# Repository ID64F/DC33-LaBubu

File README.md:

# DC33-LaBubu

## JLCPCB PCB Colors & Components
- ENIG Copper
- White Silk
- Mask
    * Red
    * Blue
    * Purple
    * Green 
    * Yellow
    * White
    * Black
- Components
    * 1206 SMD LEDs HandSoldering
    * 1206 SMD Resistors HandSoldering
    * 1206 SMD Capacitor HandSoldering
    * Attiny85
    * MCP23017
    * CR2032 Battery Holder
    * Switch
    * SAO Connector
<div align="center">

</div>
<div align="center">
 
</div>

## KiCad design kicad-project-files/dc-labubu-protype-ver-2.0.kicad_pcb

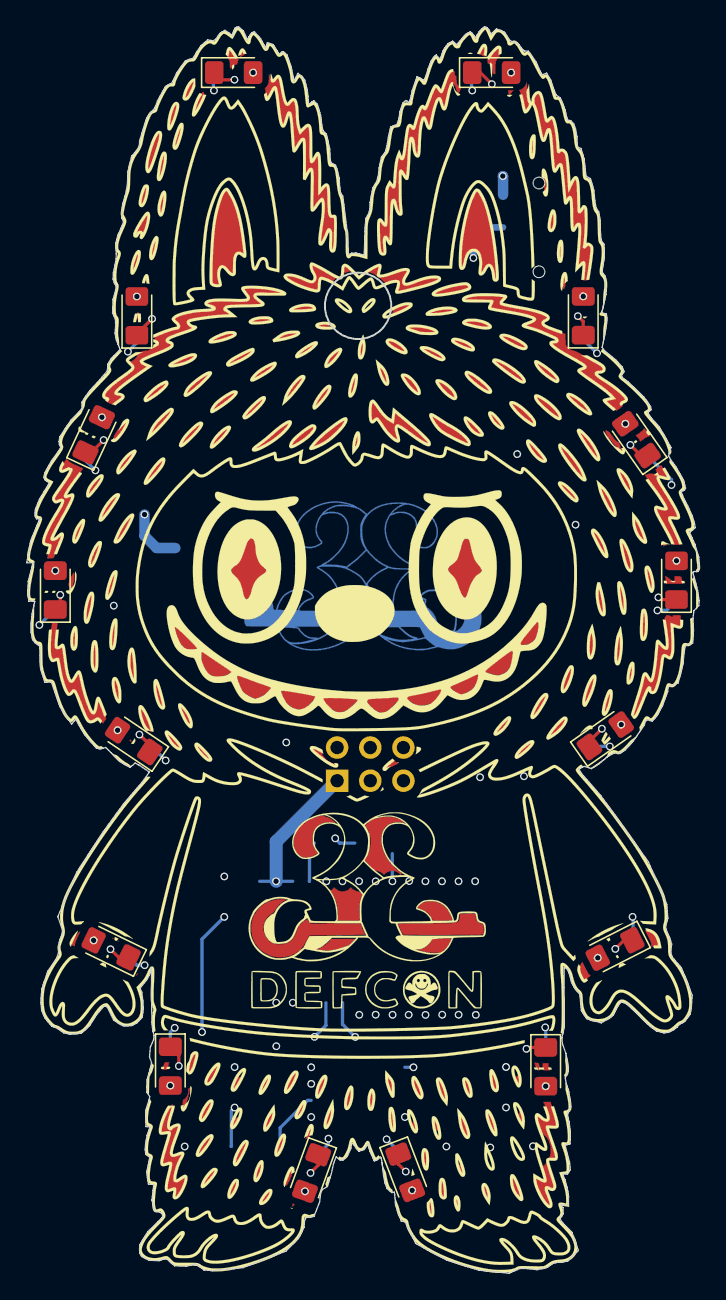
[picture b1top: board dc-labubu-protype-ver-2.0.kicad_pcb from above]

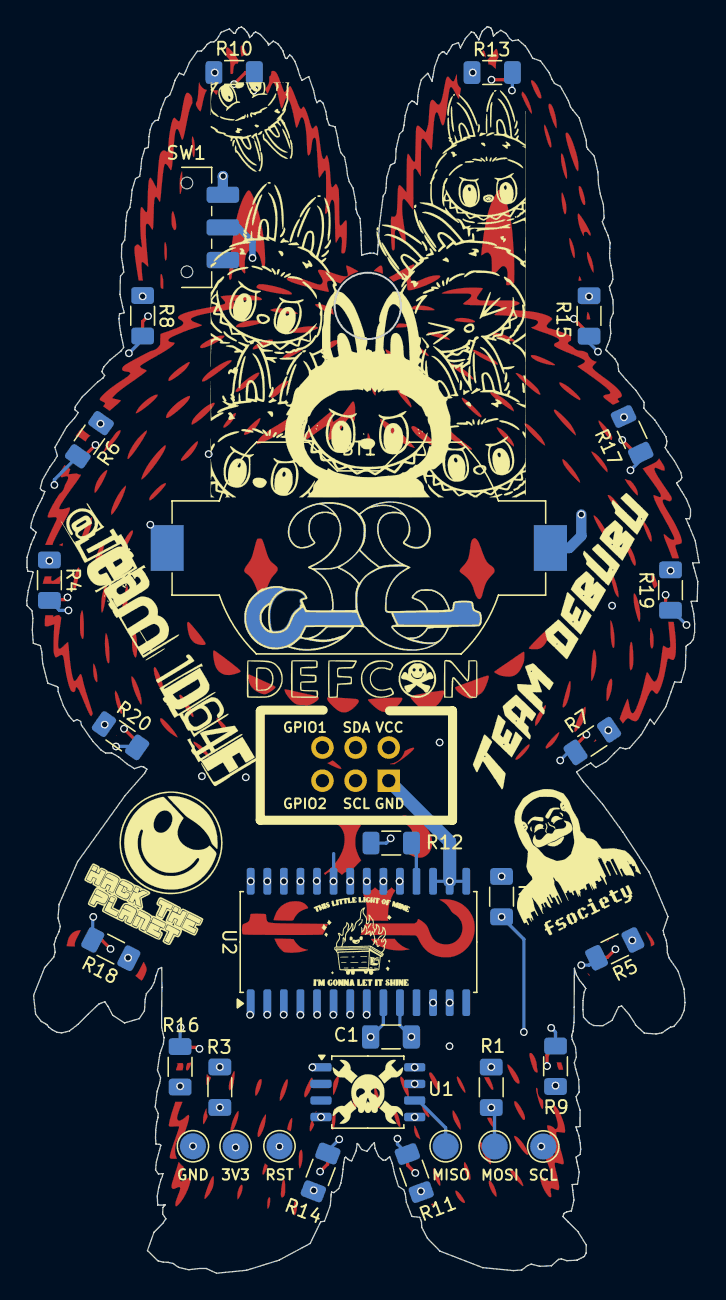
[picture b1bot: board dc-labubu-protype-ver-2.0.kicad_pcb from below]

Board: 4 copper layers, 51.5 x 95.4 mm, 49 parts (31 on the bottom side), 42 nets.

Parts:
3V3: +3V3; TestPoint_Pad_D2.0mm
BT1: Battery_Cell; BatteryHolder_Keystone_1058_1x2032
C1: 0.1µF; C_1206_3216Metric_Pad1.33x1.80mm_HandSolder
D1, D2, D3, D4, D5, D6, D7, D8, D9, D10, D11, D12, D13, D14, D15, D16: LED; LED_1206_3216Metric_Pad1.42x1.75mm_HandSolder
GND: GND; TestPoint_Pad_D2.0mm
MISO: MISO; TestPoint_Pad_D2.0mm
MOSI: MOSI (SDA); TestPoint_Pad_D2.0mm
R1, R2: 4.7k; R_1206_3216Metric_Pad1.30x1.75mm_HandSolder
R3, R12: 10kΩ; R_1206_3216Metric_Pad1.30x1.75mm_HandSolder
R4, R5, R6, R7, R8, R9, R10, R11, R13, R14, R15, R16, R17, R18, R19, R20: 220Ω; R_1206_3216Metric_Pad1.30x1.75mm_HandSolder
RST: RESET; TestPoint_Pad_D2.0mm
Ref**: Val**; dc-labubu-protype-ver-2.0
SCL: SCK (SCL); TestPoint_Pad_D2.0mm
SW1: SW_SPST; SW_SPDT_CK_JS102011SAQN
U1: ATtiny85-20S; SOIC-8_5.3x5.3mm_P1.27mm
U2: MCP23017_SO; SOIC-28W_7.5x17.9mm_P1.27mm
X1: Badgelife_sao_connector_v169bis; Badgelife-SAOv169-SAO-2x3

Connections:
+3V3: 3V3.1, C1.2, R1.1, R2.1, R3.1, R12.2, SW1.2 (B), U1.8 (VCC), U2.9 (VDD), X1.1 (VCC)
/BAT+: BT1.1 (+), SW1.1 (A)
/GPA0: R19.2, U2.21 (GPA0)
/GPA1: R17.2, U2.22 (GPA1)
/GPA2: R15.2, U2.23 (GPA2)
/GPA3: R13.2, U2.24 (GPA3)
/GPA4: R10.2, U2.25 (GPA4)
/GPA5: R8.2, U2.26 (GPA5)
/GPA6: R6.2, U2.27 (GPA6)
/GPA7: R4.2, U2.28 (GPA7)
/GPB0: R20.2, U2.1 (GPB0)
/GPB1: R18.2, U2.2 (GPB1)
/GPB2: R16.2, U2.3 (GPB2)
/GPB3: R14.2, U2.4 (GPB3)
/GPB4: R11.2, U2.5 (GPB4)
/GPB5: R9.2, U2.6 (GPB5)
/GPB6: R7.2, U2.7 (GPB6)
/GPB7: R5.2, U2.8 (GPB7)
/GPIO1: U2.20 (INTA), X1.5 (GPIO1)
/GPIO2: U2.19 (INTB), X1.6 (GPIO2)
GND: BT1.2 (-), C1.1, D1.1 (K), D2.1 (K), D3.1 (K), D4.1 (K), D5.1 (K), D6.1 (K), D7.1 (K), D8.1 (K), D9.1 (K), D10.1 (K), D11.1 (K), D12.1 (K), D13.1 (K), D14.1 (K), D15.1 (K), D16.1 (K), GND.1, U1.4 (GND), U2.10 (VSS), U2.15 (A0), U2.16 (A1), U2.17 (A2), X1.2 (GND)
MISO: MISO.1, U1.6 (PB1)
MOSI: MOSI.1, R1.2, U1.5 (AREF/PB0), U2.13 (SDA), X1.3 (SDA)
unnamed: D1.2 (A), R4.1
unnamed: D2.2 (A), R5.1
unnamed: D3.2 (A), R6.1
unnamed: D4.2 (A), R7.1
unnamed: D5.2 (A), R8.1
unnamed: D6.2 (A), R9.1
unnamed: D7.2 (A), R10.1
unnamed: D8.2 (A), R11.1
unnamed: D9.2 (A), R13.1
unnamed: D10.2 (A), R14.1
unnamed: D11.2 (A), R15.1
unnamed: D12.2 (A), R16.1
unnamed: D13.2 (A), R17.1
unnamed: D14.2 (A), R18.1
unnamed: D15.2 (A), R19.1
unnamed: D16.2 (A), R20.1
unnamed: R12.1, U2.18 (~RESET)
RESET: R3.2, RST.1, U1.1 (~RESET/PB5)
SCL: R2.2, SCL.1, U1.7 (PB2), U2.12 (SCK), X1.4 (SCL)

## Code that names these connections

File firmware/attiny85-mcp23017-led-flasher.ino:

#include <Wire.h>
#include <avr/sleep.h>
#include <avr/power.h>
#include <avr/wdt.h>

// MCP23017 I2C address (A0, A1, A2 = LOW)
#define MCP23017_ADDR 0x20

// MCP23017 Register addresses
#define MCP23017_IODIRA   0x00  // I/O Direction Register A
#define MCP23017_IODIRB   0x01  // I/O Direction Register B
#define MCP23017_GPIOA    0x12  // General Purpose I/O Port Register A
#define MCP23017_GPIOB    0x13  // General Purpose I/O Port Register B

// ATtiny85 pins for I2C (using TinyWireM library pins)
// SDA = Pin 0 (PB0)
// SCL = Pin 2 (PB2)

volatile bool wakeUp = false;

void setup() {
  // Disable unused peripherals to save power
  power_adc_disable();
  power_timer1_disable();
  
  // Initialize I2C
  Wire.begin();
  Wire.setClock(100000); // 100kHz for lower power consumption
  
  // Initialize MCP23017
  initMCP23017();
  
  // Setup watchdog timer for 1 second intervals
  setupWatchdog();
  
  // Set sleep mode
  set_sleep_mode(SLEEP_MODE_PWR_DOWN);
}

void loop() {
  // Flash each LED for 500ms
  for (uint8_t port = 0; port < 2; port++) {
    for (uint8_t pin = 0; pin < 8; pin++) {
      // Turn on current LED
      setLED(port, pin, true);
      
      // Wait 500ms using watchdog timer (sleep)
      sleepFor500ms();
      
      // Turn off current LED
      setLED(port, pin, false);
    }
  }
  
  // After cycling through all LEDs, sleep for longer period
  // to conserve battery (optional - remove if continuous cycling desired)
  for (uint8_t i = 0; i < 10; i++) { // Sleep for ~10 seconds
    sleepFor1Second();
  }
}

void initMCP23017() {
  // Set all pins as outputs (0 = output, 1 = input)
  writeRegister(MCP23017_IODIRA, 0x00); // Port A all outputs
  writeRegister(MCP23017_IODIRB, 0x00); // Port B all outputs
  
  // Turn off all LEDs initially
  writeRegister(MCP23017_GPIOA, 0x00);
  writeRegister(MCP23017_GPIOB, 0x00);
}

void writeRegister(uint8_t reg, uint8_t value) {
  Wire.beginTransmission(MCP23017_ADDR);
  Wire.write(reg);
  Wire.write(value);
  Wire.endTransmission();
  
  // Small delay to ensure I2C transaction completes
  delayMicroseconds(100);
}

uint8_t readRegister(uint8_t reg) {
  Wire.beginTransmission(MCP23017_ADDR);
  Wire.write(reg);
  Wire.endTransmission();
  
  Wire.requestFrom(MCP23017_ADDR, 1);
  return Wire.read();
}

void setLED(uint8_t port, uint8_t pin, bool state) {
  uint8_t reg = (port == 0) ? MCP23017_GPIOA : MCP23017_GPIOB;
  uint8_t currentValue = readRegister(reg);
  
  if (state) {
    currentValue |= (1 << pin);   // Set bit
  } else {
    currentValue &= ~(1 << pin);  // Clear bit
  }
  
  writeRegister(reg, currentValue);
}

void setupWatchdog() {
  // Clear the reset flag
  MCUSR &= ~(1 << WDRF);
  
  // Start timed sequence
  WDTCR |= (1 << WDCE) | (1 << WDE);
  
  // Set new watchdog timeout prescaler value to 1 second
  WDTCR = (1 << WDIE) | (1 << WDP2) | (1 << WDP1); // 1 second
}

void sleepFor1Second() {
  wakeUp = false;
  sleep_enable();
  sleep_cpu();
  sleep_disable();
}

void sleepFor500ms() {
  // For 500ms, we'll use two 250ms sleeps or approximate with delay
  // Since watchdog minimum is ~15ms, we'll use a more efficient approach
  
  // Temporarily set watchdog to shorter interval
  WDTCR |= (1 << WDCE) | (1 << WDE);
  WDTCR = (1 << WDIE) | (1 << WDP2); // ~250ms
  
  // Sleep twice for ~500ms
  sleepFor1Second();
  sleepFor1Second();
  
  // Restore 1 second watchdog
  setupWatchdog();
}

// Watchdog interrupt service routine
ISR(WDT_vect) {
  wakeUp = true;
}

/*
 * WIRING:
 * 
 * ATtiny85:
 * Pin 1 (RESET) -> 10kΩ pullup to VCC
 * Pin 4 (GND)   -> Ground
 * Pin 8 (VCC)   -> 3.3V from CR2032
 * Pin 5 (PB0)   -> SDA (MCP23017 pin 13)
 * Pin 7 (PB2)   -> SCL (MCP23017 pin 12)
 * 
 * MCP23017:
 * Pin 9 (VDD)   -> 3.3V
 * Pin 10 (VSS)  -> Ground
 * Pin 12 (SCL)  -> ATtiny85 Pin 7 (PB2) + 4.7kΩ pullup to VCC
 * Pin 13 (SDA)  -> ATtiny85 Pin 5 (PB0) + 4.7kΩ pullup to VCC
 * Pin 15 (A0)   -> Ground (sets I2C address to 0x20)
 * Pin 16 (A1)   -> Ground
 * Pin 17 (A2)   -> Ground
 * Pin 18 (RESET)-> 10kΩ pullup to VCC
 * 
 * Pins 21-28 (GPA0-GPA7) -> LEDs with appropriate current limiting resistors
 * Pins 1-8 (GPB0-GPB7)   -> LEDs with appropriate current limiting resistors
 * 
 * For 3.3V operation with typical LEDs, use ~150-220Ω current limiting resistors
 * 
 * POWER OPTIMIZATION NOTES:
 * - Uses power-down sleep mode (lowest power consumption)
 * - Disables unused peripherals (ADC, Timer1)
 * - Uses watchdog timer for timing instead of active delays
 * - I2C at 100kHz for lower power consumption
 * - LEDs are only on for 500ms each, minimizing current draw
 * - Optional longer sleep periods between LED cycles
 */

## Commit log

2025-08-02 added gerber directory, SVGs and footprints
2025-08-02 Added kicad-project-files directory and going to add firmware and instructions directory
2025-08-02 added arduino firmware code to flash SAOs once assembled
2025-08-02 added png file where components are placed
2025-08-02 unhide the layers for the pcb from the svg image
2025-08-02 Added pcb colors that were orderd through JLCPCB
2025-08-02 added images and details for pcbs that were ordered
2025-08-02 centered the images making it easier to view
